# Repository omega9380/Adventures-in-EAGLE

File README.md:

# Adventures-in-EAGLE
My haphazard designs playing with Autodesk EAGLE

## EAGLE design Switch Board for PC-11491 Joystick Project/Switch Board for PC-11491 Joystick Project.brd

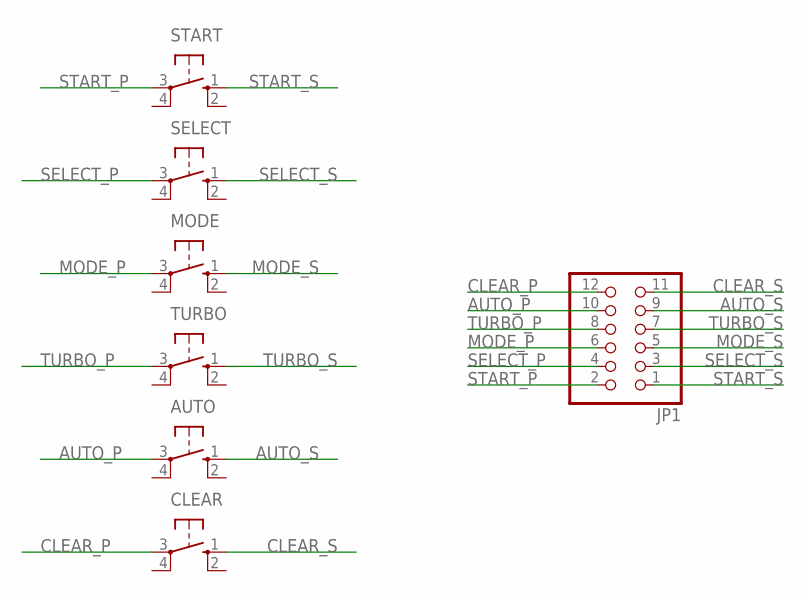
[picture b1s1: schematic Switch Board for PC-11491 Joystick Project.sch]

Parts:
AUTO: 10-XX; B3F-10XX
CLEAR: 10-XX; B3F-10XX
JP1: PINHD-2X6; 2X06
MODE: 10-XX; B3F-10XX
SELECT: 10-XX; B3F-10XX
START: 10-XX; B3F-10XX
TURBO: 10-XX; B3F-10XX

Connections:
AUTO_P: AUTO.3, JP1.10
AUTO_S: AUTO.1 (S), JP1.9
CLEAR_P: CLEAR.3, JP1.12
CLEAR_S: CLEAR.1 (S), JP1.11
MODE_P: JP1.6, MODE.3
MODE_S: JP1.5, MODE.1 (S)
SELECT_P: JP1.4, SELECT.3
SELECT_S: JP1.3, SELECT.1 (S)
START_P: JP1.2, START.3
START_S: JP1.1, START.1 (S)
TURBO_P: JP1.8, TURBO.3
TURBO_S: JP1.7, TURBO.1 (S)

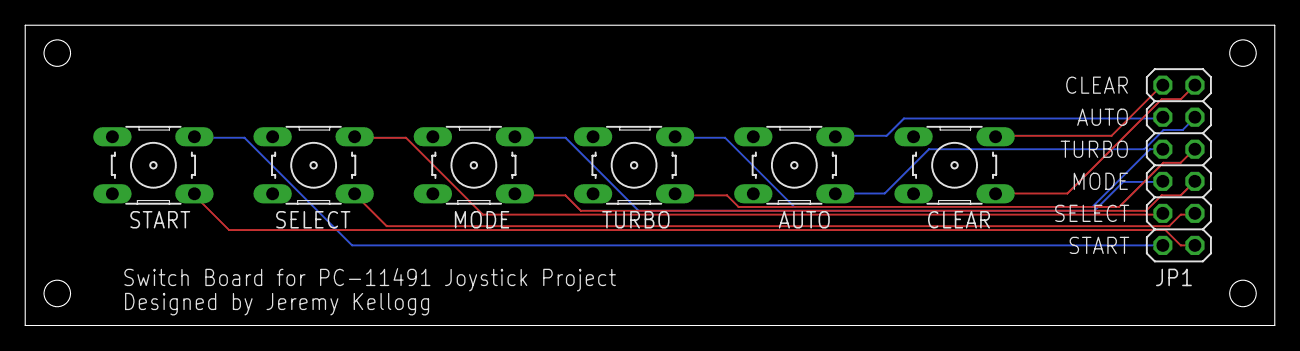
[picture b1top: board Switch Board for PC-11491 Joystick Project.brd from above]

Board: 2 copper layers, 99.0 x 23.8 mm, 7 parts (0 on the bottom side), 12 nets.

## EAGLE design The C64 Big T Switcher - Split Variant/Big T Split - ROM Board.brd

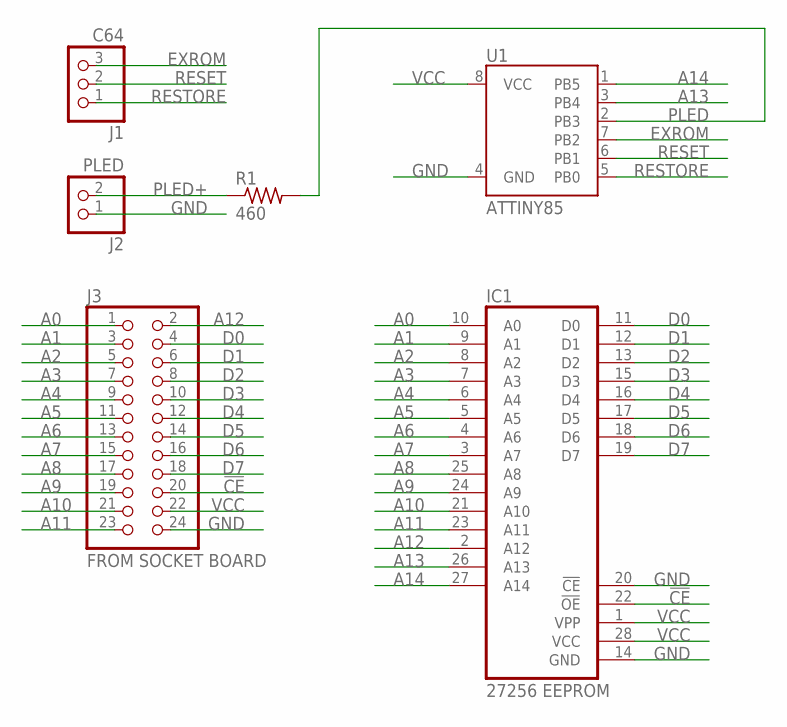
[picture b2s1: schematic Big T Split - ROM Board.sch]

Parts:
IC1: 27256 EEPROM; DIL28
J1: C64; 1X03
J2: PLED; 1X02
J3: FROM SOCKET BOARD; 2X12
R1: 460; R0805
U1: ATTINY85

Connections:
!CE: IC1.22 (!OE), J3.20
A0: IC1.10 (A0), J3.1
A1: IC1.9 (A1), J3.3
A2: IC1.8 (A2), J3.5
A3: IC1.7 (A3), J3.7
A4: IC1.6 (A4), J3.9
A5: IC1.5 (A5), J3.11
A6: IC1.4 (A6), J3.13
A7: IC1.3 (A7), J3.15
A8: IC1.25 (A8), J3.17
A9: IC1.24 (A9), J3.19
A10: IC1.21 (A10), J3.21
A11: IC1.23 (A11), J3.23
A12: IC1.2 (A12), J3.2
A13: IC1.26 (A13), U1.3 (PB4)
A14: IC1.27 (A14), U1.1 (PB5)
D0: IC1.11 (D0), J3.4
D1: IC1.12 (D1), J3.6
D2: IC1.13 (D2), J3.8
D3: IC1.15 (D3), J3.10
D4: IC1.16 (D4), J3.12
D5: IC1.17 (D5), J3.14
D6: IC1.18 (D6), J3.16
D7: IC1.19 (D7), J3.18
EXROM: J1.3, U1.7 (PB2)
GND: IC1.14 (GND), IC1.20 (!CE), J2.1, J3.24, U1.4 (GND)
PLED: R1.2, U1.2 (PB3)
PLED+: J2.2, R1.1
RESET: J1.2, U1.6 (PB1)
RESTORE: J1.1, U1.5 (PB0)
VCC: IC1.1 (VPP), IC1.28 (VCC), J3.22, U1.8 (VCC)

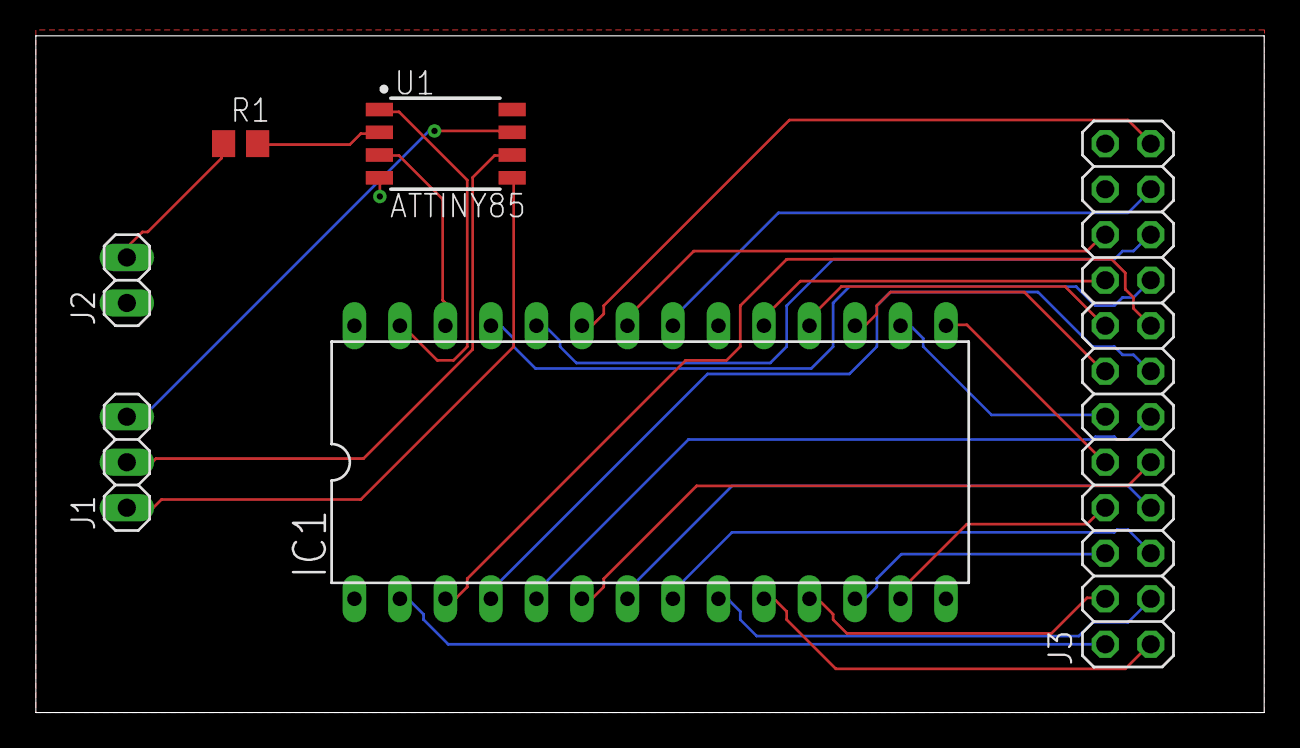
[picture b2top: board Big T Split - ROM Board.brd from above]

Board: 2 copper layers, 68.6 x 37.8 mm, 6 parts (0 on the bottom side), 31 nets.

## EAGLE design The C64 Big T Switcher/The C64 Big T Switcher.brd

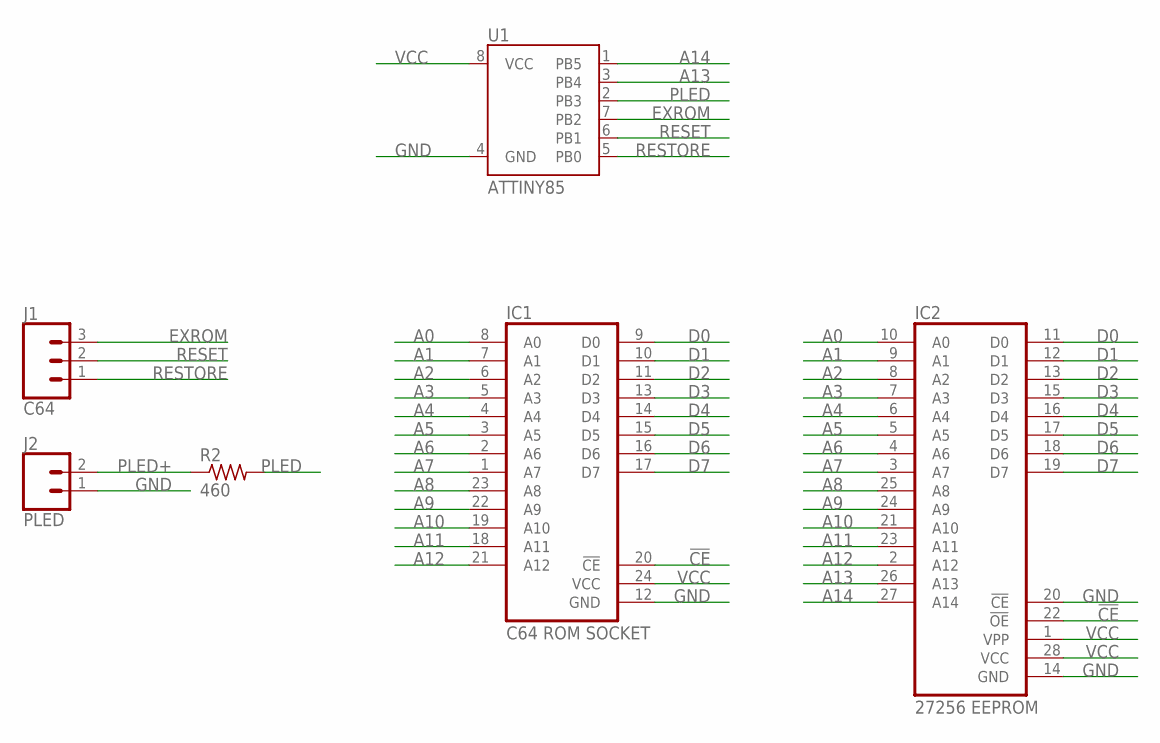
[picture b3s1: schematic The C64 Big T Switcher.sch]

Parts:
IC1: C64 ROM SOCKET; DIL24
IC2: 27256 EEPROM; DIL28
J1: C64; 1X03
J2: PLED; 1X02
R2: 460; 0207/10
U1: ATTINY85

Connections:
!CE: IC1.20 (!CE), IC2.22 (!OE)
A0: IC1.8 (A0), IC2.10 (A0)
A1: IC1.7 (A1), IC2.9 (A1)
A2: IC1.6 (A2), IC2.8 (A2)
A3: IC1.5 (A3), IC2.7 (A3)
A4: IC1.4 (A4), IC2.6 (A4)
A5: IC1.3 (A5), IC2.5 (A5)
A6: IC1.2 (A6), IC2.4 (A6)
A7: IC1.1 (A7), IC2.3 (A7)
A8: IC1.23 (A8), IC2.25 (A8)
A9: IC1.22 (A9), IC2.24 (A9)
A10: IC1.19 (A10), IC2.21 (A10)
A11: IC1.18 (A11), IC2.23 (A11)
A12: IC1.21 (A12), IC2.2 (A12)
A13: IC2.26 (A13), U1.3 (PB4)
A14: IC2.27 (A14), U1.1 (PB5)
D0: IC1.9 (D0), IC2.11 (D0)
D1: IC1.10 (D1), IC2.12 (D1)
D2: IC1.11 (D2), IC2.13 (D2)
D3: IC1.13 (D3), IC2.15 (D3)
D4: IC1.14 (D4), IC2.16 (D4)
D5: IC1.15 (D5), IC2.17 (D5)
D6: IC1.16 (D6), IC2.18 (D6)
D7: IC1.17 (D7), IC2.19 (D7)
EXROM: J1.3, U1.7 (PB2)
GND: IC1.12 (GND), IC2.14 (GND), IC2.20 (!CE), J2.1, U1.4 (GND)
PLED: R2.2, U1.2 (PB3)
PLED+: J2.2, R2.1
RESET: J1.2, U1.6 (PB1)
RESTORE: J1.1, U1.5 (PB0)
VCC: IC1.24 (VCC), IC2.1 (VPP), IC2.28 (VCC), U1.8 (VCC)

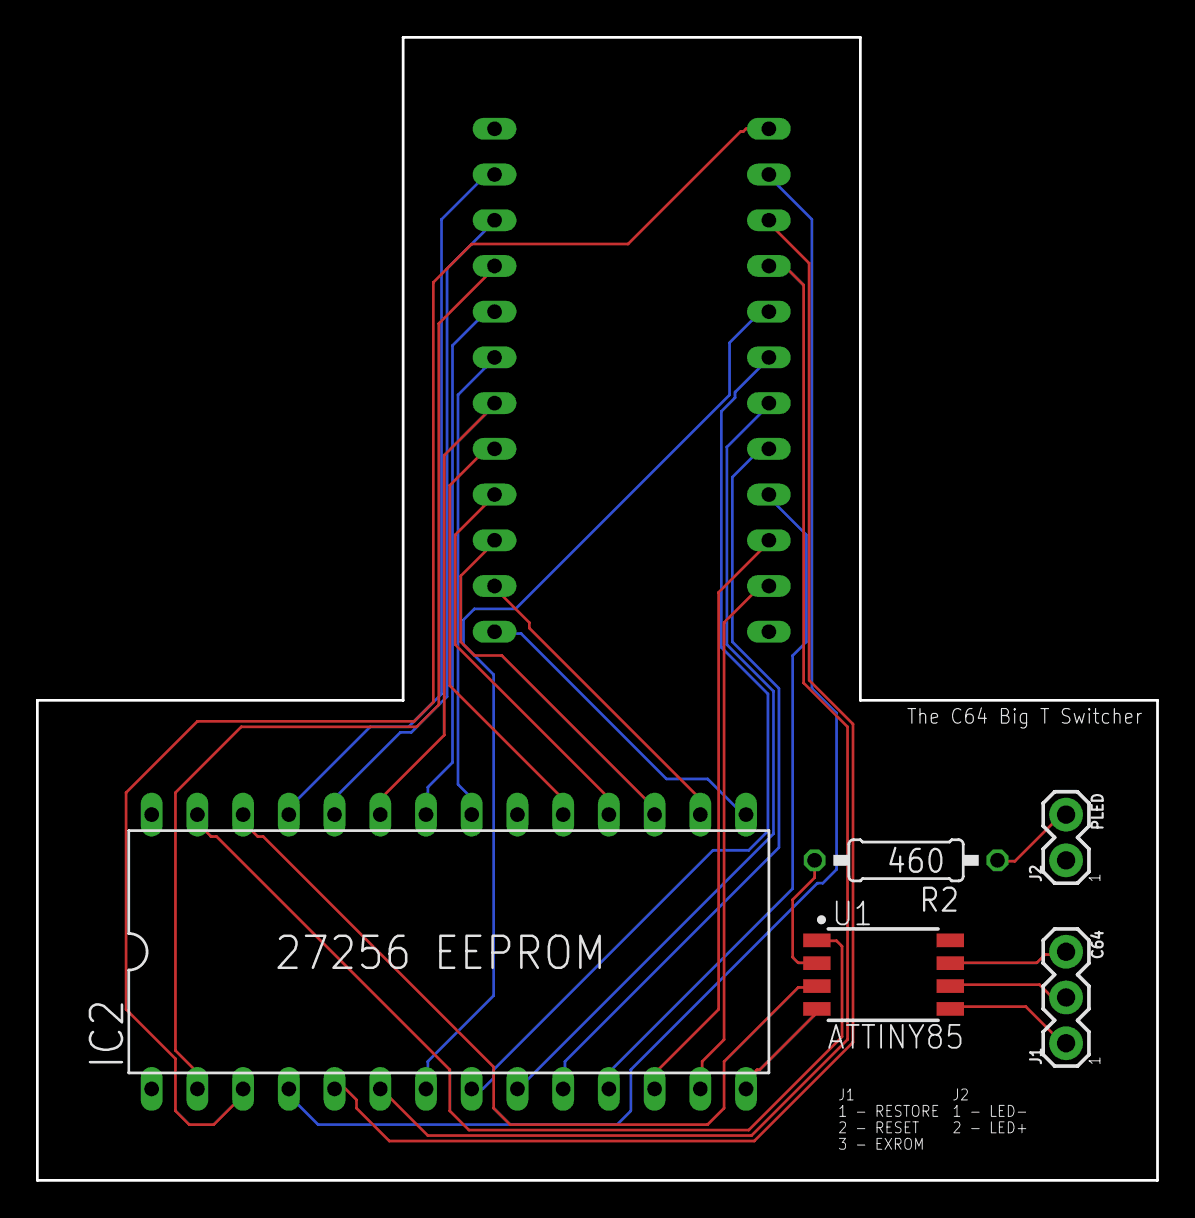
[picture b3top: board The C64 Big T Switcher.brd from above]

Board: 2 copper layers, 62.2 x 63.5 mm, 6 parts (1 on the bottom side), 31 nets.

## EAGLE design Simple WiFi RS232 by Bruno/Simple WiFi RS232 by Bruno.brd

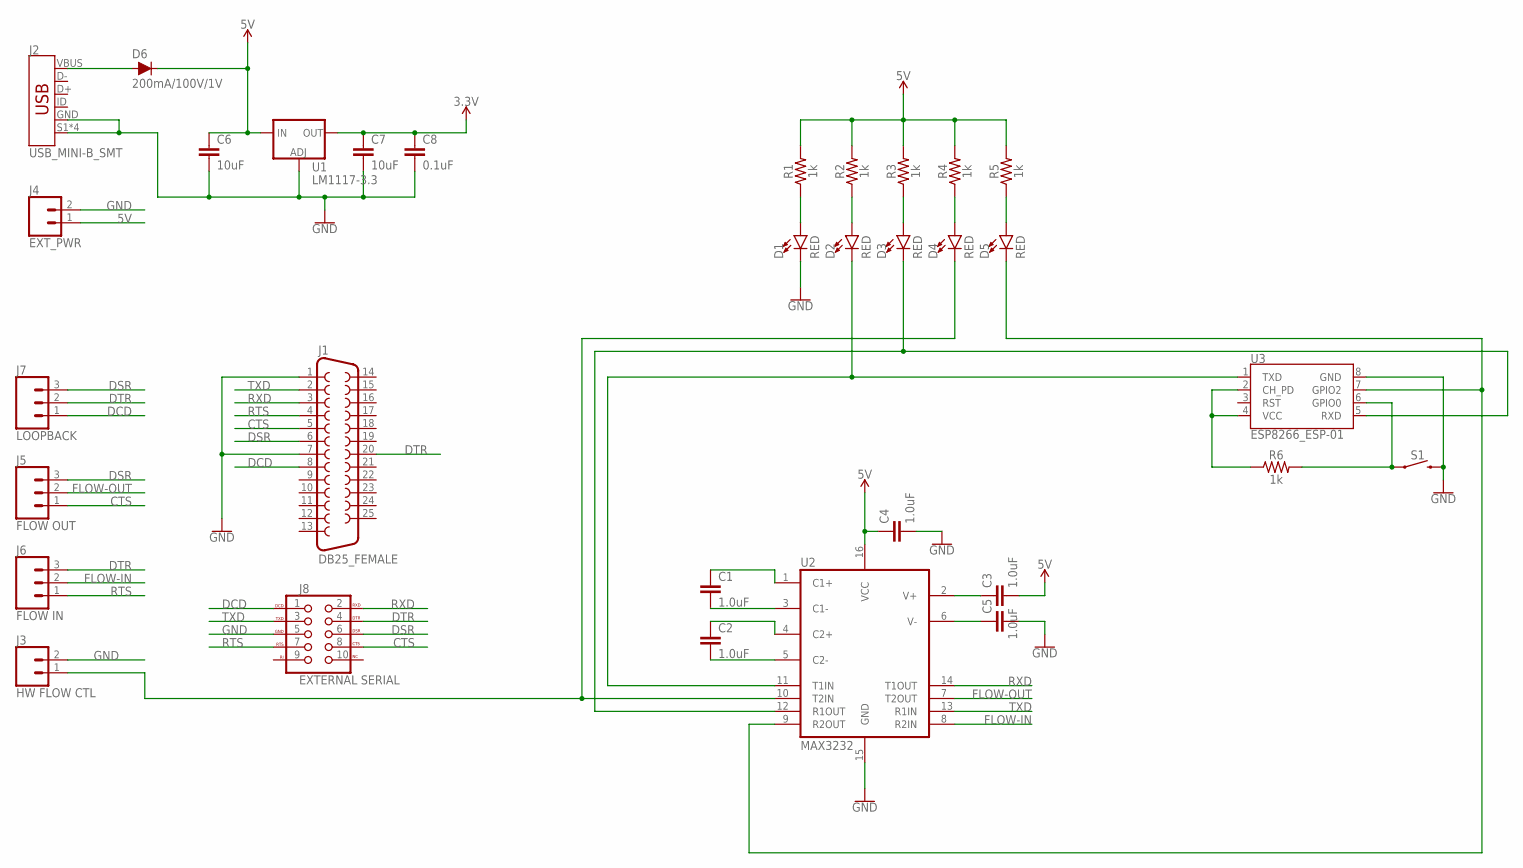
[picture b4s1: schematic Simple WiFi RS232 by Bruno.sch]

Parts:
C1, C2, C3, C4, C5: 1.0uF; 0603
C6, C7: 10uF; 0603
C8: 0.1uF; 0603
D1, D2, D3, D4, D5: RED; LED-0603
D6: 200mA/100V/1V; DIODE-1N4148
J1: DB25_FEMALE; F25HP
J2: USB_MINI-B_SMT; USB-MINIB
J3: HW FLOW CTL; 1X02
J4: EXT_PWR; 1X02
J5: FLOW OUT; 1X03
J6: FLOW IN; 1X03
J7: LOOPBACK; 1X03
J8: EXTERNAL SERIAL; 2X5-SHROUDED
R1, R2, R3, R4, R5, R6: 1k; 0603
S1: MOMENTARY-SWITCH-SPST-PTH-6.0MM; TACTILE_SWITCH_PTH_6.0MM
U1: LM1117-3.3; SOT223
U2: MAX3232; DIP16
U3: ESP8266_ESP-01

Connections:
3.3V: C7.1, C8.1, U1.2 (OUT), U1.4 (OUT)
5V: C3.2, C4.1, C6.1, D6.C, J4.1, R1.2, R2.2, R3.2, R4.2, R5.2, U1.3 (IN), U2.16 (VCC)
CTS: J1.5, J5.1, J8.8 (CTS)
DCD: J1.8, J7.1, J8.1 (DCD)
DSR: J1.6, J5.3, J7.3, J8.6 (DSR)
DTR: J1.20, J6.3, J7.2, J8.4 (DTR)
FLOW-IN: J6.2, U2.8 (R2IN)
FLOW-OUT: J5.2, U2.7 (T2OUT)
GND: C4.2, C5.2, C6.2, C7.2, C8.2, D1.C, J1.1, J1.7, J2.GND, J2.S1 (SHIELD), J2.S2 (SHIELD), J2.S3 (SHIELD), J2.S4 (SHIELD), J3.2, J4.2, J8.5 (GND), S1.3 (2), U1.1 (ADJ), U2.15 (GND), U3.8 (GND)
unnamed: R6.2, S1.1, U3.6 (GPIO0)
unnamed: C1.1, U2.1 (C1+)
unnamed: C1.2, U2.3 (C1-)
unnamed: C2.1, U2.4 (C2+)
unnamed: C2.2, U2.5 (C2-)
unnamed: C3.1, U2.2 (V+)
unnamed: C5.1, U2.6 (V-)
unnamed: D1.A, R1.1
unnamed: D2.A, R2.1
unnamed: D3.A, R3.1
unnamed: D4.A, R4.1
unnamed: D5.A, R5.1
unnamed: R6.1, U3.2 (CH_PD), U3.4 (VCC)
unnamed: D6.A, J2.VBUS
unnamed: D4.C, J3.1, U2.10 (T2IN)
unnamed: D2.C, U2.11 (T1IN), U3.1 (TXD)
unnamed: D3.C, U2.12 (R1OUT), U3.5 (RXD)
unnamed: D5.C, U2.9 (R2OUT), U3.7 (GPIO2)
NC: J8.10 (NC)
RTS: J1.4, J6.1, J8.7 (RTS)
RXD: J1.3, J8.2 (RXD), U2.14 (T1OUT)
TXD: J1.2, J8.3 (TXD), U2.13 (R1IN)

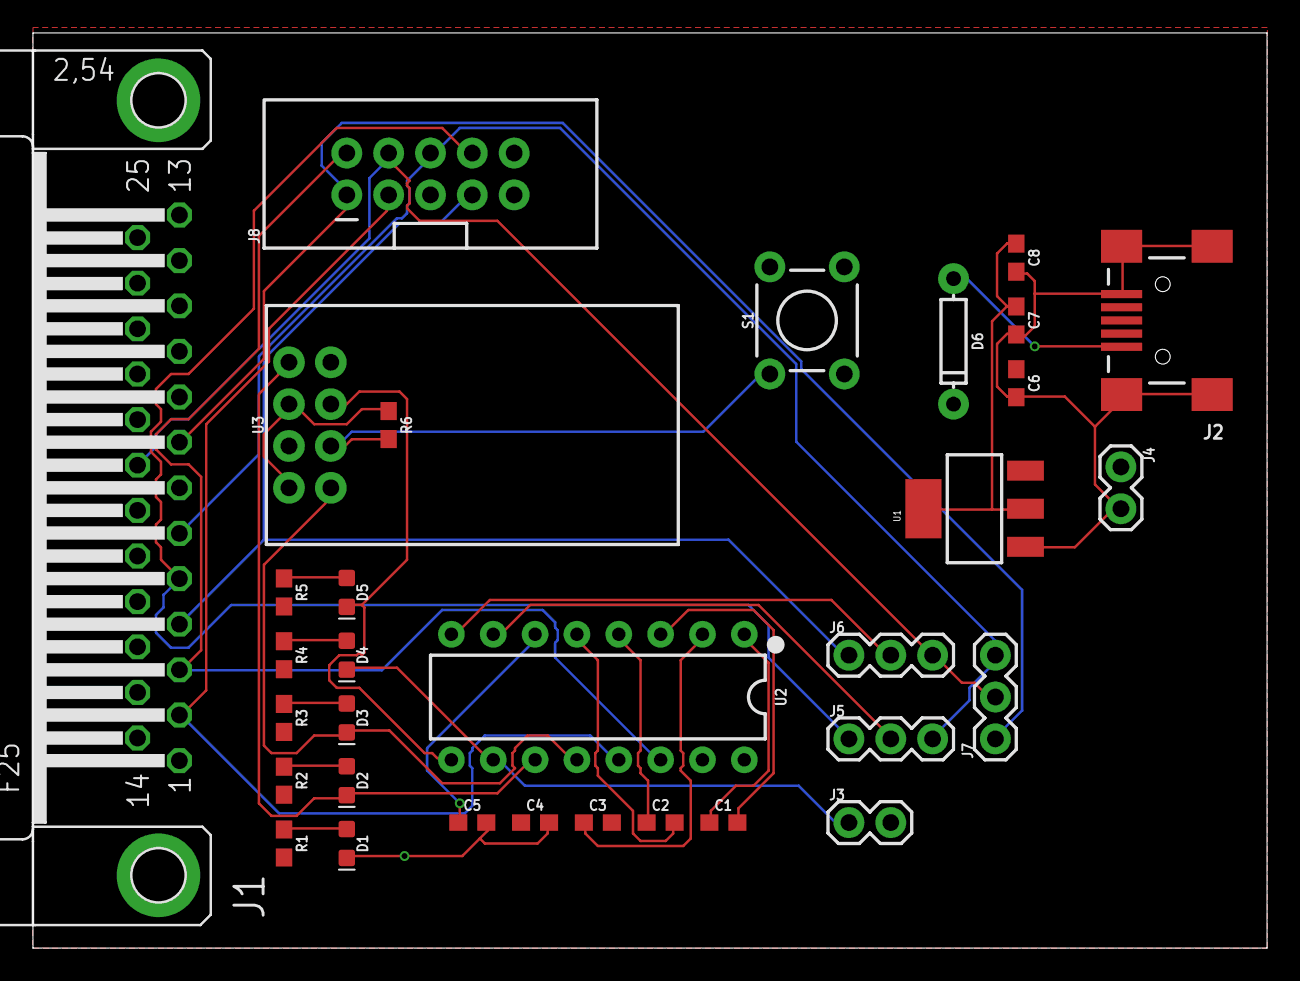
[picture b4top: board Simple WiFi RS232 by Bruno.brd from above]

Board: 2 copper layers, 74.9 x 55.5 mm, 32 parts (0 on the bottom side), 30 nets.

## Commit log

2020-05-13 Moved designs into Github
2020-05-13 Removed JOB files, created Readmes
2020-05-13 Modified GOTEK board to add 4 pin header for speaker
2020-05-13 Binglesprat
2020-05-13 Baldurdash
2020-05-13 Removed autorouter files - C64 ROM Selector
2020-05-14 Finished C64 Rom Selector
2020-05-14 Corrected missing trace in Gotek speaker circuit
2020-05-14 Minor edits to labels
2020-05-21 Minor updates to schematic design for C64 selector board
2020-05-21 Created PDFs of all boards and schematics
2020-05-21 Created C64 ROM Selector - ATMega328
    C64 ROM Selector simplified by removing full Arduino and replacing with dedicated ATMega328 chip
2020-05-22 Finished C64 ROM Selector - ATMega version
2020-05-22 Hid vRestrict layer so crystal would show on PDF
2020-05-23 Fixed FTDI header pinout (Was backwards)
2020-05-28 Created C64 ROM Selector - ATTiny85
    New ROM selector board using ATTiny85, suggested by Adrian
2020-05-28 Updated schematic to clarify pins
2020-05-31 bLAH
2020-06-08 Renamed Rom Selector (ATTiny85) to Big T Switcher
2020-06-08 Created 2 board split variant of Big T
2020-07-30 Update Commit
    Haven't commited in forever, sending an update!
2020-08-21 Sync Commit
2020-08-25 Working on Breakouts
2020-08-26 Breakout Boards done
2020-08-26 More expansion board work

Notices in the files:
parts and their libraries:
SparkFun-Capacitors: Licensing: Creative Commons ShareAlike 4.0 International - https://creativecommons.org/licenses/by-sa/4.0
